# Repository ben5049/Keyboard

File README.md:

# Keyboard

## V3

Features:
- Wireless
    - 900mAh battery
    - Bluetooth (nRF52)
    - ZMK
- 4 Port USB hub
- BLDC Knob for haptic feedback
- Kailh Choc V1 switches

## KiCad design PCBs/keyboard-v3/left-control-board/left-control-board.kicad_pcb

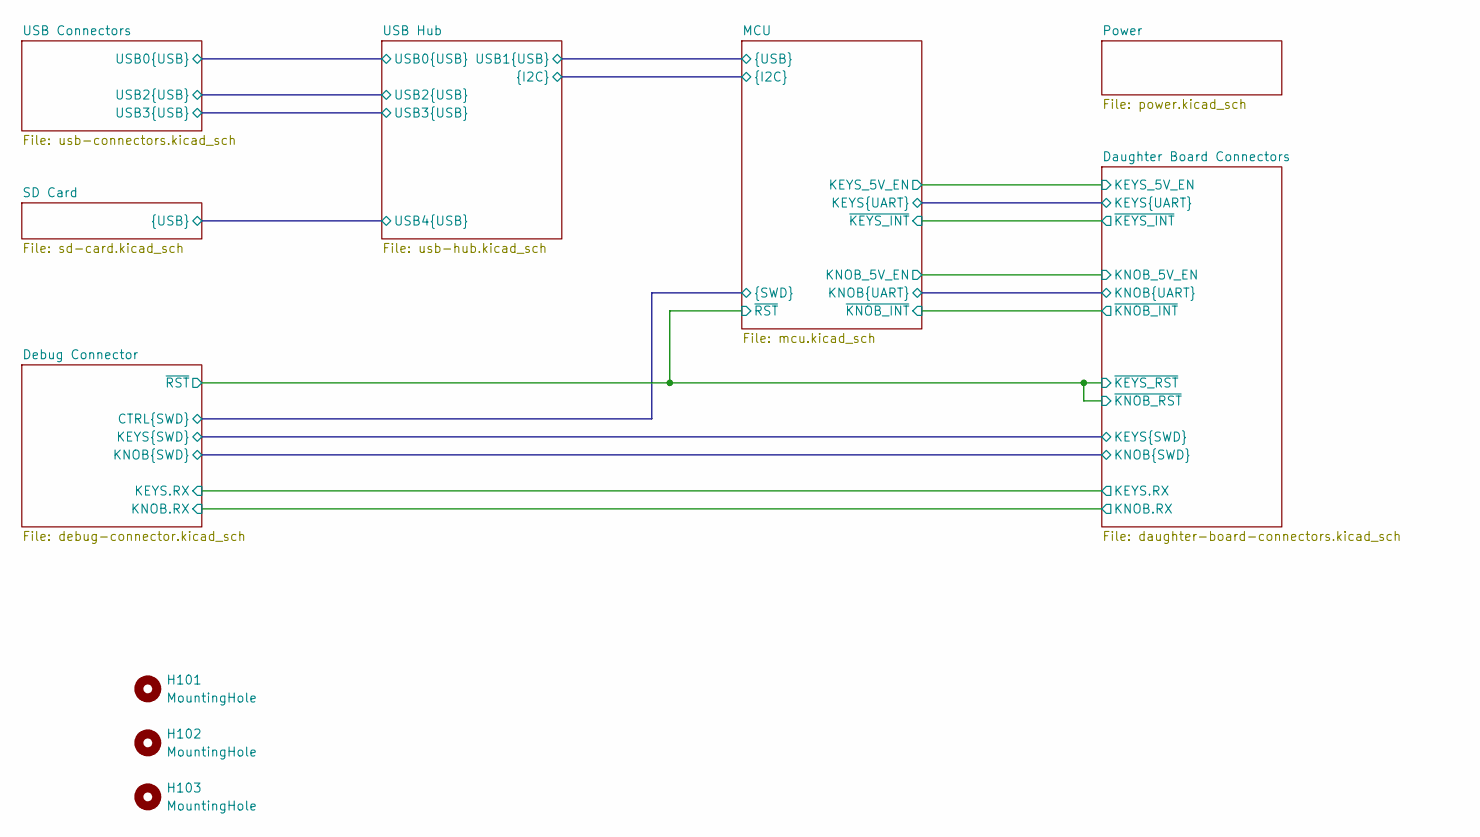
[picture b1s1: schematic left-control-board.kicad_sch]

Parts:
H101, H102, H103: MountingHole; MountingHole_2.2mm_M2

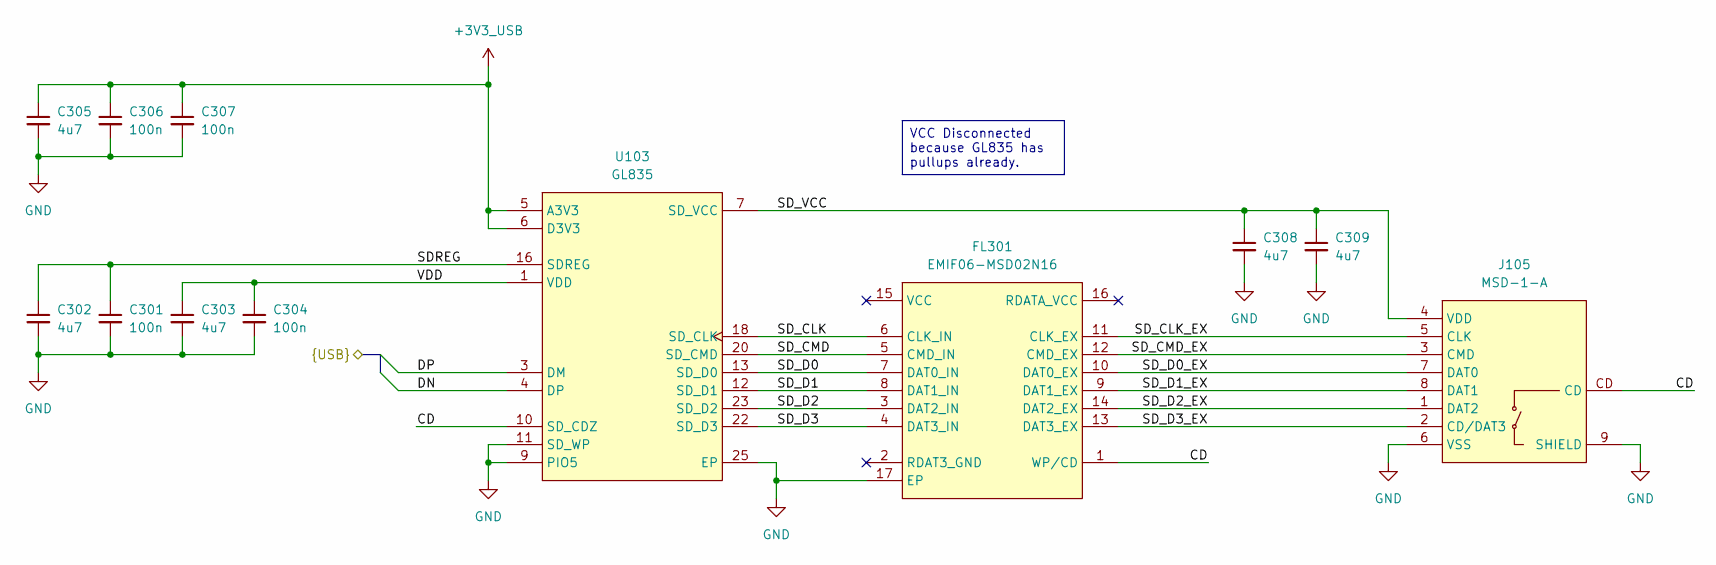
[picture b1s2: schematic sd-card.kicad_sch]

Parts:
C301, C304, C306, C307: 100n; C_0402
C302, C303, C305, C308, C309: 4u7; C_0402
FL301: EMIF06-MSD02N16; EMIF06MSD02N16
J105: MSD-1-A; MSD1A
U103: GL835; QFN50P400X400X100-25N-D

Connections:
+3V3_USB: C305.1, C306.1, C307.1, U103.5 (A3V3), U103.6 (D3V3); also elsewhere on the board
/SD Card/CD: FL301.1 (WP/CD), J105.CD, U103.10 (SD_CDZ)
/SD Card/DN: U103.4 (DP); also elsewhere on the board
/SD Card/DP: U103.3 (DM); also elsewhere on the board
/SD Card/SDREG: C301.1, C302.1, U103.16 (SDREG)
/SD Card/SD_CLK: FL301.6 (CLK_IN), U103.18 (SD_CLK)
/SD Card/SD_CLK_EX: FL301.11 (CLK_EX), J105.5 (CLK)
/SD Card/SD_CMD: FL301.5 (CMD_IN), U103.20 (SD_CMD)
/SD Card/SD_CMD_EX: FL301.12 (CMD_EX), J105.3 (CMD)
/SD Card/SD_D0: FL301.7 (DAT0_IN), U103.13 (SD_D0)
/SD Card/SD_D0_EX: FL301.10 (DAT0_EX), J105.7 (DAT0)
/SD Card/SD_D1: FL301.8 (DAT1_IN), U103.12 (SD_D1)
/SD Card/SD_D1_EX: FL301.9 (DAT1_EX), J105.8 (DAT1)
/SD Card/SD_D2: FL301.3 (DAT2_IN), U103.23 (SD_D2)
/SD Card/SD_D2_EX: FL301.14 (DAT2_EX), J105.1 (DAT2)
/SD Card/SD_D3: FL301.4 (DAT3_IN), U103.22 (SD_D3)
/SD Card/SD_D3_EX: FL301.13 (DAT3_EX), J105.2 (CD/DAT3)
/SD Card/SD_VCC: C308.1, C309.1, J105.4 (VDD), U103.7 (SD_VCC)
/SD Card/VDD: C303.1, C304.1, U103.1 (VDD)
GND: C301.2, C302.2, C303.2, C304.2, C305.2, C306.2, C307.2, C308.2, C309.2, FL301.17 (EP), J105.6 (VSS), J105.9 (SHIELD), J105.10 (SHIELD), J105.11 (SHIELD), J105.12 (SHIELD), U103.9 (PIO5), U103.11 (SD_WP), U103.25 (EP); also elsewhere on the board

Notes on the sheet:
VCC Disconnected because GL835 has pullups already.

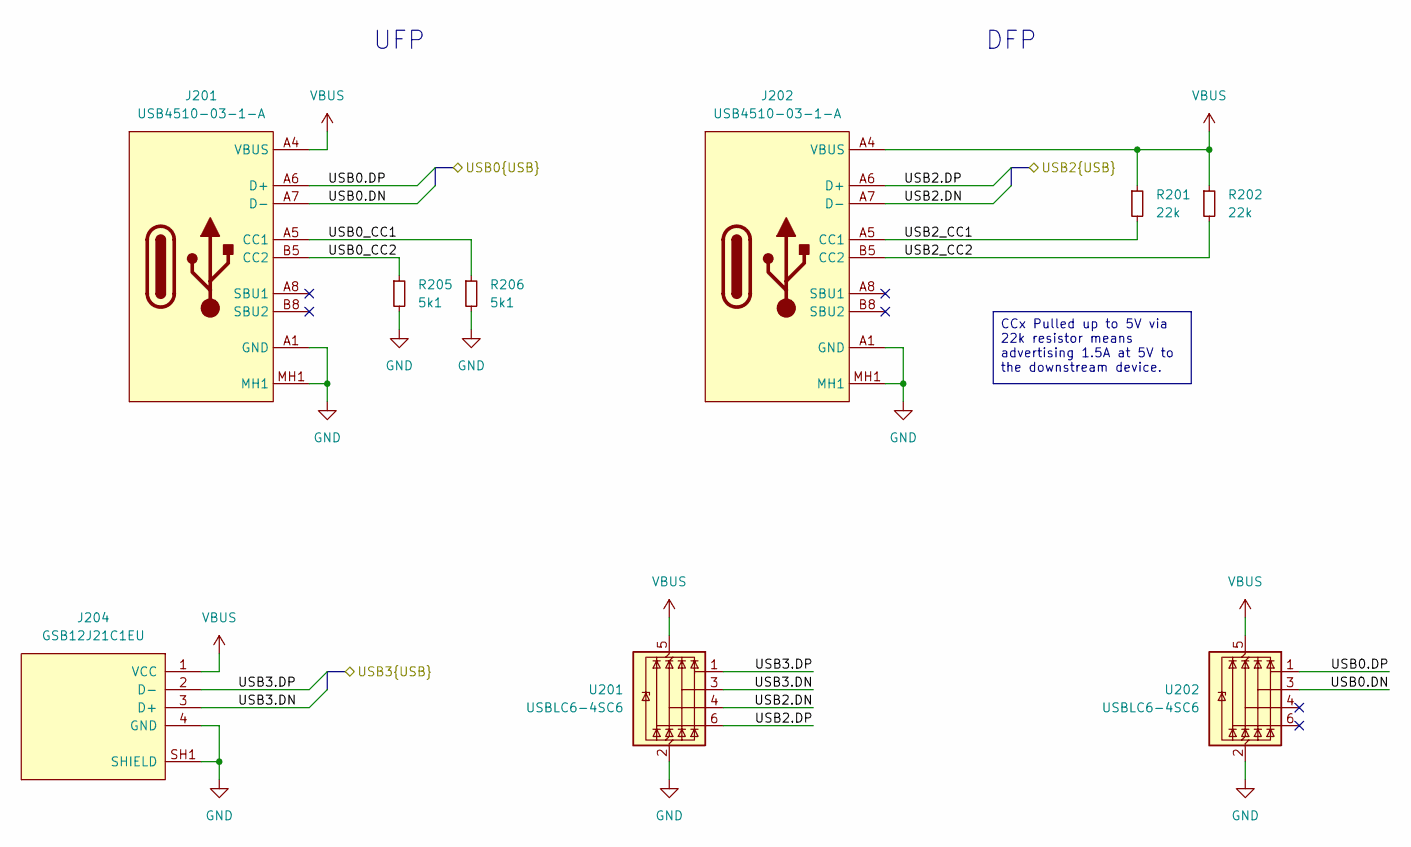
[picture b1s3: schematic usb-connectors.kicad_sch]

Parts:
J201, J202: USB4510-03-1-A; USB4510031A; Mouser Part Number 640-USB4510031A
J204: GSB12J21C1EU
R201, R202: 22k; R_0402
R205, R206: 5k1; R_0402
U201, U202: USBLC6-4SC6; SOT-23-6

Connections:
/USB Connectors/USB0.DN: J201.A7 (D-), J201.B7 (D-), U202.3 (I/O2); also elsewhere on the board
/USB Connectors/USB0.DP: J201.A6 (D+), J201.B6 (D+), U202.1 (I/O1); also elsewhere on the board
/USB Connectors/USB0_CC1: J201.A5 (CC1), R206.1
/USB Connectors/USB0_CC2: J201.B5 (CC2), R205.1
/USB Connectors/USB2.DN: J202.A7 (D-), J202.B7 (D-), U201.4 (I/O3); also elsewhere on the board
/USB Connectors/USB2.DP: J202.A6 (D+), J202.B6 (D+), U201.6 (I/O4); also elsewhere on the board
/USB Connectors/USB2_CC1: J202.A5 (CC1), R201.2
/USB Connectors/USB2_CC2: J202.B5 (CC2), R202.2
/USB Connectors/USB3.DN: J204.3 (D+), U201.3 (I/O2); also elsewhere on the board
/USB Connectors/USB3.DP: J204.2 (D-), U201.1 (I/O1); also elsewhere on the board
GND: J201.A1 (GND), J201.A12 (GND), J201.MH1, J201.MH2, J201.MH3, J201.MH4, J202.A1 (GND), J202.A12 (GND), J202.MH1, J202.MH2, J202.MH3, J202.MH4, J204.4 (GND), J204.SH1 (SHIELD), J204.SH2 (SHIELD), J204.SH3 (SHIELD), J204.SH4 (SHIELD), R205.2, R206.2, U201.2 (GND), U202.2 (GND); also elsewhere on the board
VBUS: J201.A4 (VBUS), J201.A9 (VBUS), J202.A4 (VBUS), J202.A9 (VBUS), J204.1 (VCC), R201.1, R202.1, U201.5 (VBUS), U202.5 (VBUS); also elsewhere on the board

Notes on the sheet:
UFP
DFP
CCx Pulled up to 5V via 22k resistor means advertising 1.5A at 5V to the downstream device.

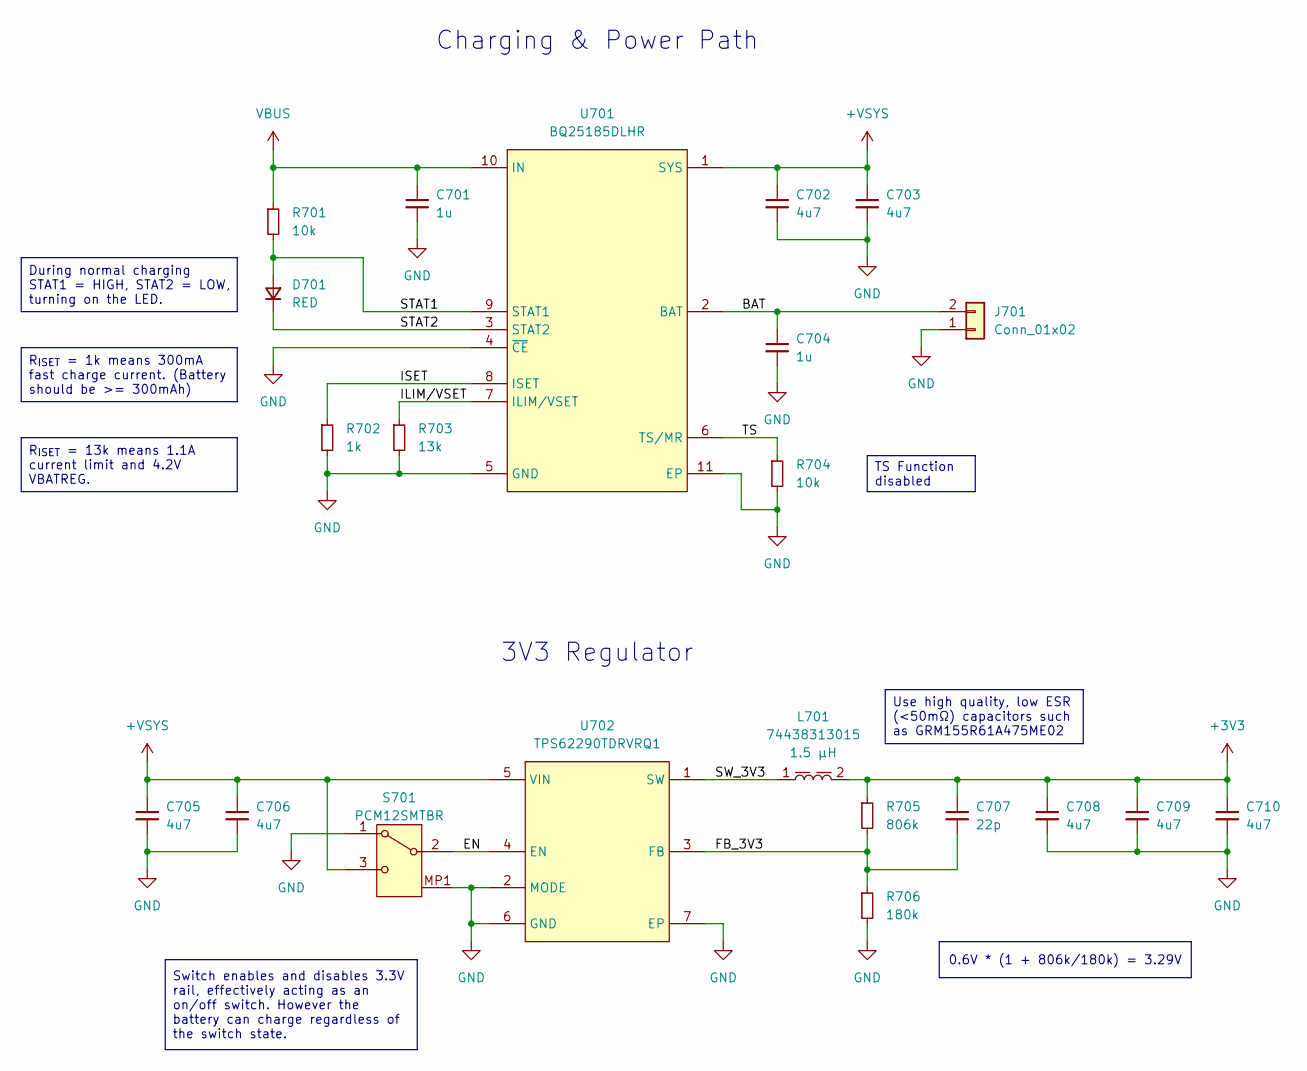
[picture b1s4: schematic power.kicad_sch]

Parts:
C701, C704: 1u; C_0402
C702, C703, C705, C706, C708, C709, C710: 4u7; C_0402
C707: 22p; C_0402
D701: RED; LED_0402
J701: Conn_01x02; JST_PH_S2B-PH-K_1x02_P2.00mm_Horizontal
L701: 74438313015; L_Wurth_WE-MAPI-1610; Part Number 74438313015
R701, R704: 10k; R_0402
R702: 1k; R_0402
R703: 13k; R_0402
R705: 806k; R_0402
R706: 180k; R_0402
S701: PCM12SMTBR
U701: BQ25185DLHR; SON40P220X200X80-11N
U702: TPS62290TDRVRQ1; SON65P200X200X80-7N; Mouser Part Number 595-TPS62290TDRVRQ1

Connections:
+3V3: C707.1, C708.1, C709.1, C710.1, L701.2, R705.1; also elsewhere on the board
+VSYS: C702.1, C703.1, C705.1, C706.1, S701.3 (NO), U701.1 (SYS), U702.5 (VIN); also elsewhere on the board
/Power/BAT: C704.1, J701.2, U701.2 (BAT)
/Power/EN: S701.2 (COM), U702.4 (EN)
/Power/FB_3V3: C707.2, R705.2, R706.1, U702.3 (FB)
/Power/ILIM/VSET: R703.1, U701.7 (ILIM/VSET)
/Power/ISET: R702.1, U701.8 (ISET)
/Power/STAT1: D701.2 (A), R701.2, U701.9 (STAT1)
/Power/STAT2: D701.1 (K), U701.3 (STAT2)
/Power/SW_3V3: L701.1, U702.1 (SW)
/Power/TS: R704.1, U701.6 (TS/MR)
GND: C701.2, C702.2, C703.2, C704.2, C705.2, C706.2, C708.2, C709.2, C710.2, J701.1, R702.2, R703.2, R704.2, R706.2, S701.1 (NC), S701.MP1, S701.MP2, S701.MP3, S701.MP4, U701.4 (~CE), U701.5 (GND), U701.11 (EP), U702.2 (MODE), U702.6 (GND), U702.7 (EP); also elsewhere on the board
VBUS: C701.1, R701.1, U701.10 (IN); also elsewhere on the board

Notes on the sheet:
3V3 Regulator
Charging & Power Path
Switch enables and disables 3.3V rail, effectively acting as an on/off switch. However the battery can charge regardless of the switch state.
0.6V * (1 + 806k/180k) = 3.29V
During normal charging STAT1 = HIGH, STAT2 = LOW, turning on the LED.
Use high quality, low ESR (<50mΩ) capacitors such as GRM155R61A475ME02
R_{ISET} = 1k means 300mA fast charge current. (Battery should be >= 300mAh)
R_{ISET} = 13k means 1.1A current limit and 4.2V VBATREG.
TS Function disabled

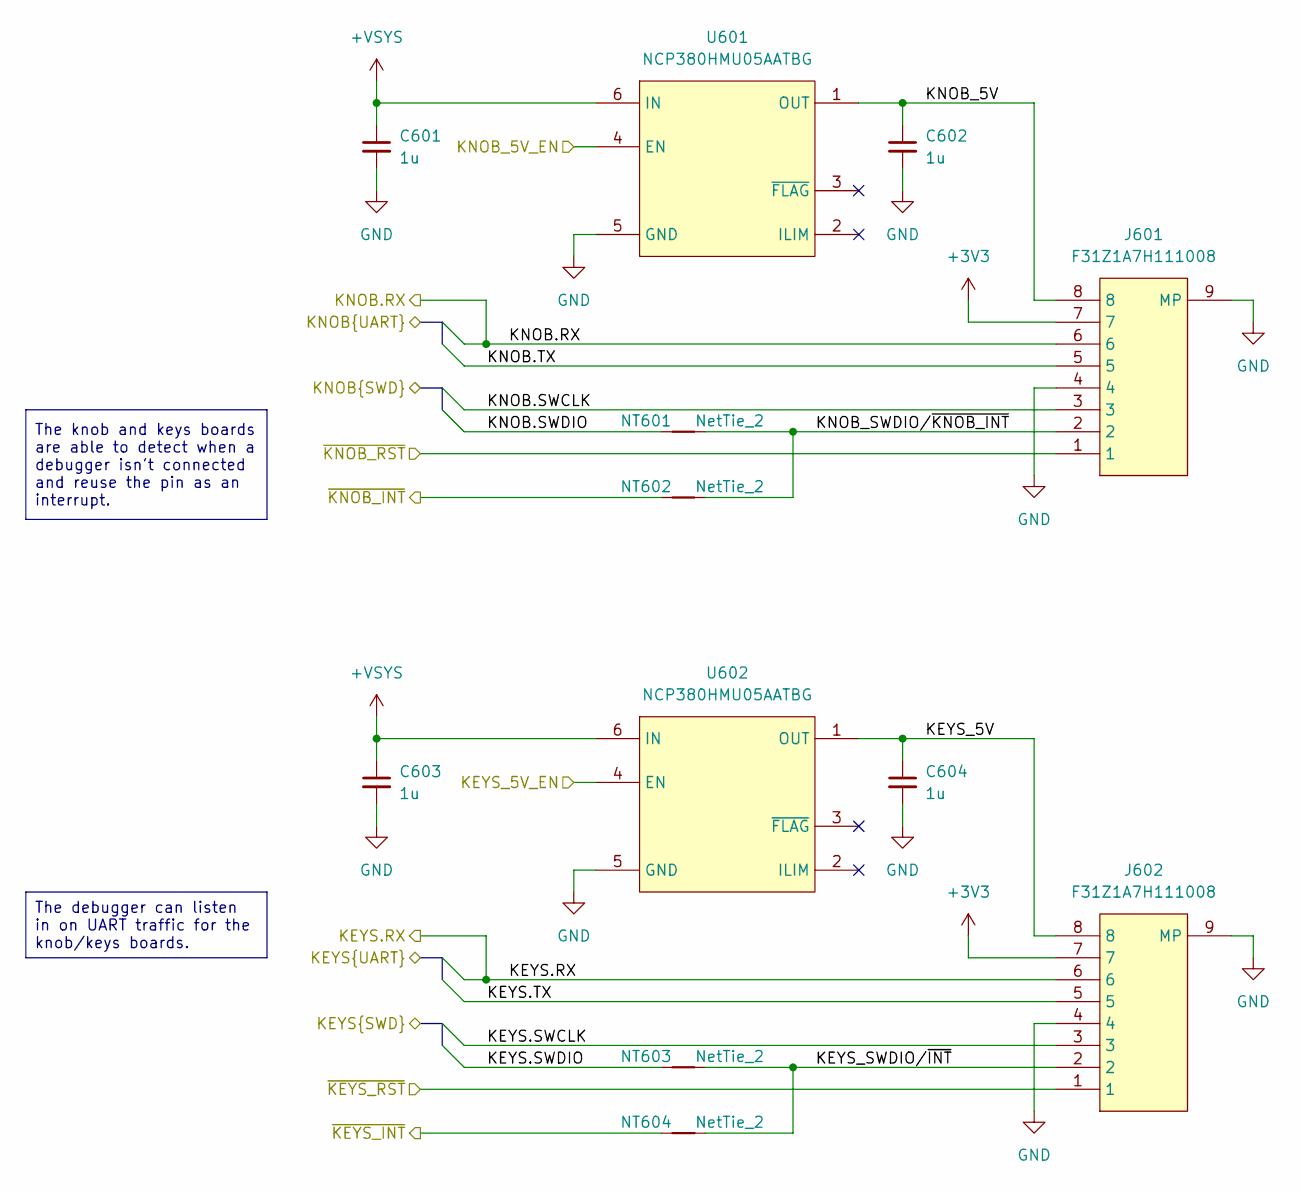
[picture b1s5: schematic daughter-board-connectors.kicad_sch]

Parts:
C601, C602, C603, C604: 1u; C_0402
J601, J602: F31Z1A7H111008
NT601, NT602, NT603, NT604: NetTie_2; NetTie-2_SMD_Pad0.15mm
U601, U602: NCP380HMU05AATBG; SON65P200X200X55-7N

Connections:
+3V3: J601.7, J602.7; also elsewhere on the board
+VSYS: C601.1, C603.1, U601.6 (IN), U602.6 (IN); also elsewhere on the board
/Daughter Board Connectors/KEYS.RX: J602.6; also elsewhere on the board
/Daughter Board Connectors/KEYS.SWCLK: J602.3; also elsewhere on the board
/Daughter Board Connectors/KEYS.SWDIO: NT603.1; also elsewhere on the board
/Daughter Board Connectors/KEYS.TX: J602.5; also elsewhere on the board
/Daughter Board Connectors/KEYS_5V: C604.1, J602.8, U602.1 (OUT)
/Daughter Board Connectors/KEYS_5V_EN: U602.4 (EN); also elsewhere on the board
/Daughter Board Connectors/KEYS_SWDIO/~INT: J602.2, NT603.2, NT604.2
/Daughter Board Connectors/KNOB.RX: J601.6; also elsewhere on the board
/Daughter Board Connectors/KNOB.SWCLK: J601.3; also elsewhere on the board
/Daughter Board Connectors/KNOB.SWDIO: NT601.1; also elsewhere on the board
/Daughter Board Connectors/KNOB.TX: J601.5; also elsewhere on the board
/Daughter Board Connectors/KNOB_5V: C602.1, J601.8, U601.1 (OUT)
/Daughter Board Connectors/KNOB_5V_EN: U601.4 (EN); also elsewhere on the board
/Daughter Board Connectors/KNOB_SWDIO/~KNOB_INT: J601.2, NT601.2, NT602.2
/Daughter Board Connectors/~KEYS_INT: NT604.1; also elsewhere on the board
/Daughter Board Connectors/~KEYS_RST: J601.1, J602.1; also elsewhere on the board
/Daughter Board Connectors/~KNOB_INT: NT602.1; also elsewhere on the board
GND: C601.2, C602.2, C603.2, C604.2, J601.4, J601.9 (MP), J601.10 (MP), J601.11 (MP), J601.12 (MP), J602.4, J602.9 (MP), J602.10 (MP), J602.11 (MP), J602.12 (MP), U601.5 (GND), U601.7 (GND), U602.5 (GND), U602.7 (GND); also elsewhere on the board

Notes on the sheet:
The debugger can listen in on UART traffic for the knob/keys boards.
The knob and keys boards are able to detect when a debugger isn't connected and reuse the pin as an interrupt.

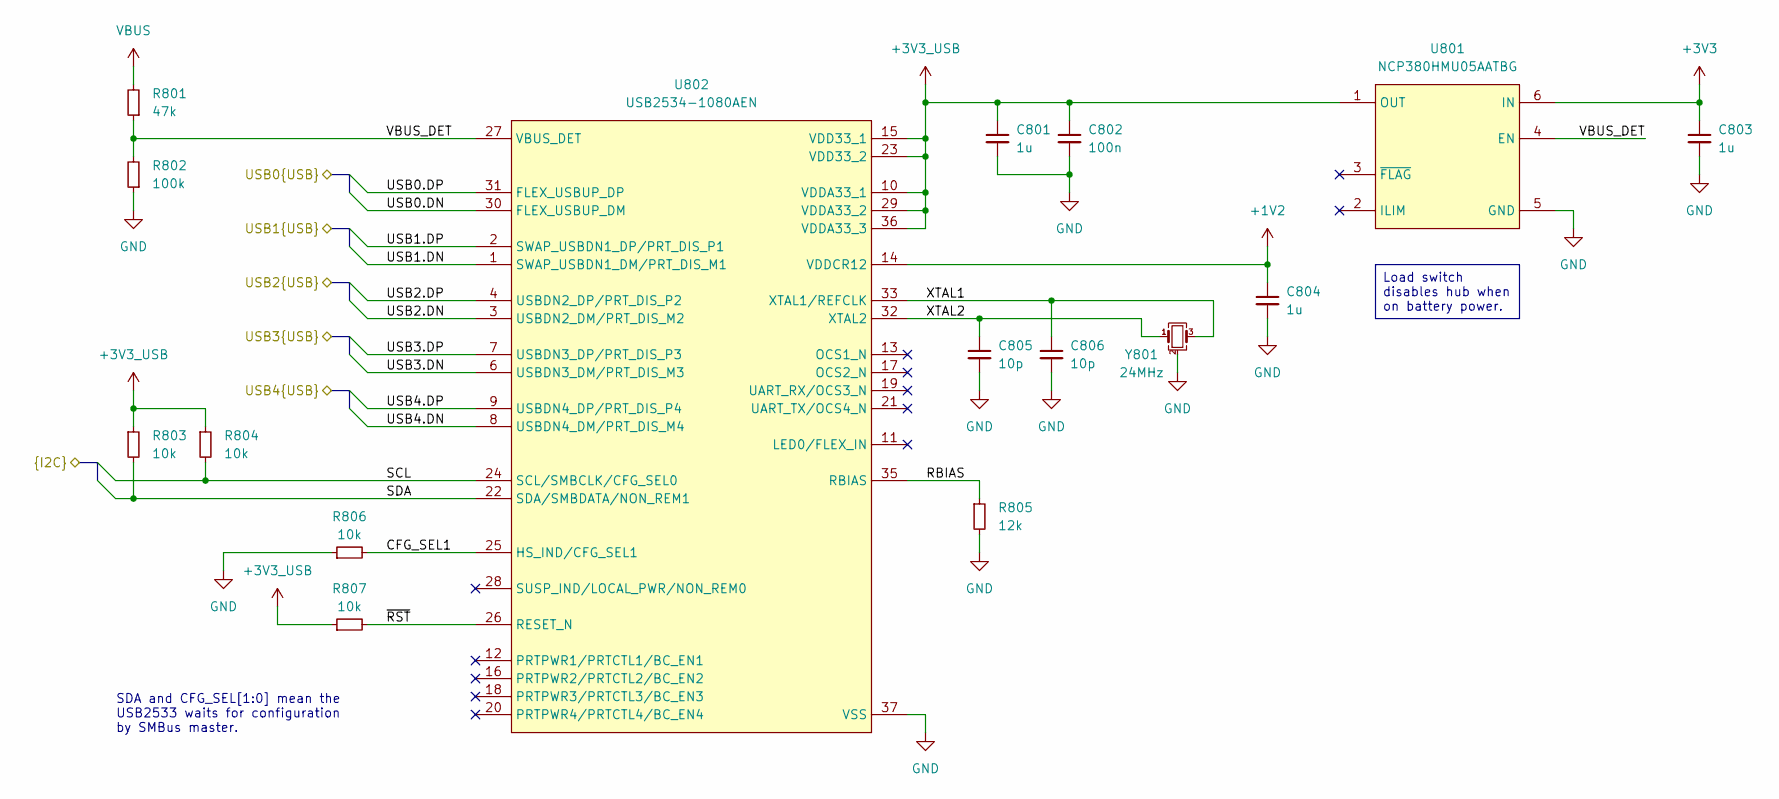
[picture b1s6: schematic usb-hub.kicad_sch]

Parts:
C801, C803, C804: 1u; C_0402
C802: 100n; C_0402
C805, C806: 10p; C_0402
R801: 47k; R_0402
R802: 100k; R_0402
R803, R804, R806, R807: 10k; R_0402
R805: 12k; R_0402
U801: NCP380HMU05AATBG; SON65P200X200X55-7N
U802: USB2534-1080AEN; QFN50P600X600X100-37N-D
Y801: CX2016SA24000D0HLLG3; Crystal_SMD_2016-4Pin_2.0x1.6mm

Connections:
+1V2: C804.1, U802.14 (VDDCR12)
+3V3: C803.1, U801.6 (IN); also elsewhere on the board
+3V3_USB: C801.1, C802.1, R803.1, R804.1, R807.1, U801.1 (OUT), U802.10 (VDDA33_1), U802.15 (VDD33_1), U802.23 (VDD33_2), U802.29 (VDDA33_2), U802.36 (VDDA33_3); also elsewhere on the board
/MCU/DN: U802.1 (SWAP_USBDN1_DM/PRT_DIS_M1); also elsewhere on the board
/MCU/DP: U802.2 (SWAP_USBDN1_DP/PRT_DIS_P1); also elsewhere on the board
/MCU/SCL: R804.2, U802.24 (SCL/SMBCLK/CFG_SEL0); also elsewhere on the board
/MCU/SDA: R803.2, U802.22 (SDA/SMBDATA/NON_REM1); also elsewhere on the board
/SD Card/DN: U802.8 (USBDN4_DM/PRT_DIS_M4); also elsewhere on the board
/SD Card/DP: U802.9 (USBDN4_DP/PRT_DIS_P4); also elsewhere on the board
/USB Connectors/USB0.DN: U802.30 (FLEX_USBUP_DM); also elsewhere on the board
/USB Connectors/USB0.DP: U802.31 (FLEX_USBUP_DP); also elsewhere on the board
/USB Connectors/USB2.DN: U802.3 (USBDN2_DM/PRT_DIS_M2); also elsewhere on the board
/USB Connectors/USB2.DP: U802.4 (USBDN2_DP/PRT_DIS_P2); also elsewhere on the board
/USB Connectors/USB3.DN: U802.6 (USBDN3_DM/PRT_DIS_M3); also elsewhere on the board
/USB Connectors/USB3.DP: U802.7 (USBDN3_DP/PRT_DIS_P3); also elsewhere on the board
/USB Hub/CFG_SEL1: R806.2, U802.25 (HS_IND/CFG_SEL1)
/USB Hub/RBIAS: R805.1, U802.35 (RBIAS)
/USB Hub/VBUS_DET: R801.1, R802.2, U801.4 (EN), U802.27 (VBUS_DET)
/USB Hub/XTAL1: C806.1, U802.33 (XTAL1/REFCLK), Y801.3
/USB Hub/XTAL2: C805.1, U802.32 (XTAL2), Y801.1
/USB Hub/~RST: R807.2, U802.26 (RESET_N)
GND: C801.2, C802.2, C803.2, C804.2, C805.2, C806.2, R802.1, R805.2, R806.1, U801.5 (GND), U801.7 (GND), U802.37 (VSS), Y801.2 (G), Y801.4 (G); also elsewhere on the board
VBUS: R801.2; also elsewhere on the board

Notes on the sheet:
SDA and CFG_SEL[1:0] mean the USB2533 waits for configuration by SMBus master.
Load switch disables hub when on battery power.

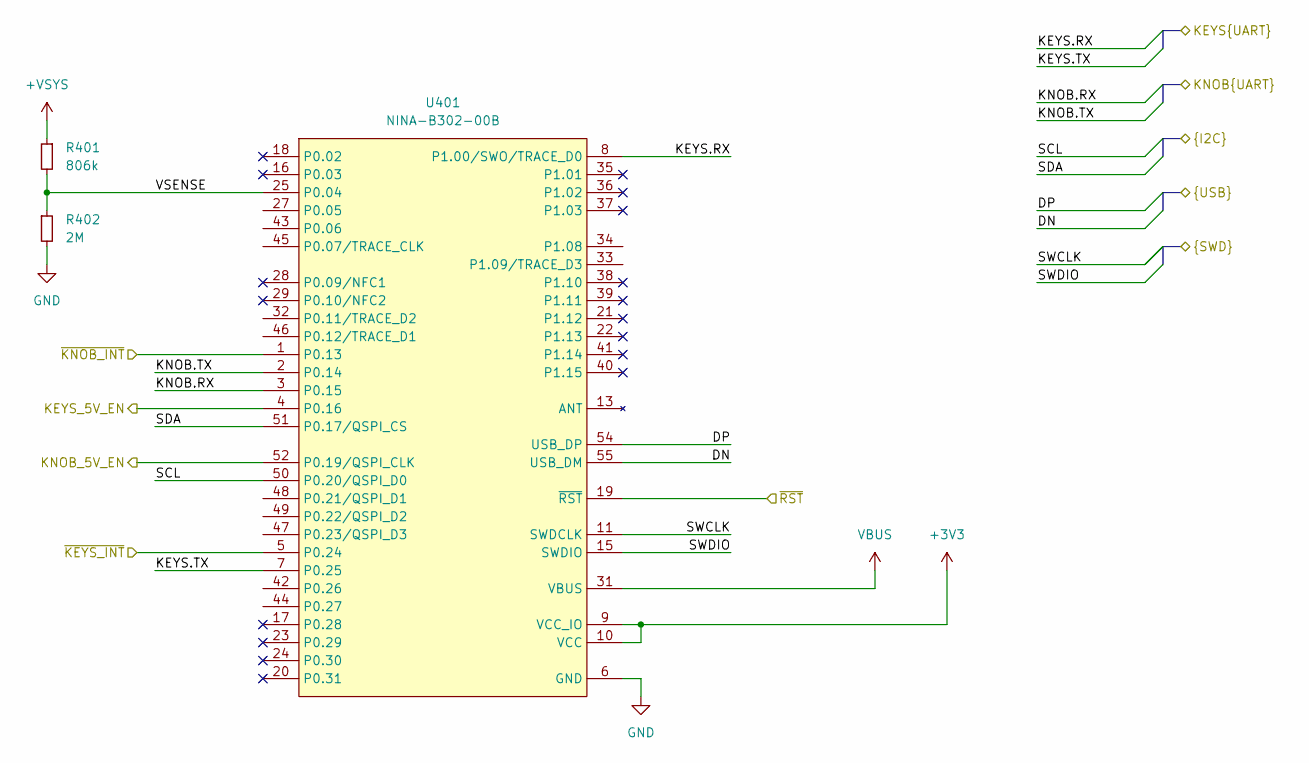
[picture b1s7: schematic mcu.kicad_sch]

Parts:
R401: 806k; R_0402
R402: 2M; R_0402
U401: NINA-B302-00B; NINAB30200B

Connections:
+3V3: U401.9 (VCC_IO), U401.10 (VCC); also elsewhere on the board
+VSYS: R401.1; also elsewhere on the board
/Daughter Board Connectors/KEYS.RX: U401.8 (P1.00/SWO/TRACE_D0); also elsewhere on the board
/Daughter Board Connectors/KEYS.TX: U401.7 (P0.25); also elsewhere on the board
/Daughter Board Connectors/KEYS_5V_EN: U401.4 (P0.16); also elsewhere on the board
/Daughter Board Connectors/KNOB.RX: U401.3 (P0.15); also elsewhere on the board
/Daughter Board Connectors/KNOB.TX: U401.2 (P0.14); also elsewhere on the board
/Daughter Board Connectors/KNOB_5V_EN: U401.52 (P0.19/QSPI_CLK); also elsewhere on the board
/Daughter Board Connectors/~KEYS_INT: U401.5 (P0.24); also elsewhere on the board
/Daughter Board Connectors/~KEYS_RST: U401.19 (~RST); also elsewhere on the board
/Daughter Board Connectors/~KNOB_INT: U401.1 (P0.13); also elsewhere on the board
/Debug Connector/CTRL.SWCLK: U401.11 (SWDCLK); also elsewhere on the board
/Debug Connector/CTRL.SWDIO: U401.15 (SWDIO); also elsewhere on the board
/MCU/DN: U401.55 (USB_DM); also elsewhere on the board
/MCU/DP: U401.54 (USB_DP); also elsewhere on the board
/MCU/SCL: U401.50 (P0.20/QSPI_D0); also elsewhere on the board
/MCU/SDA: U401.51 (P0.17/QSPI_CS); also elsewhere on the board
/MCU/VSENSE: R401.2, R402.1, U401.25 (P0.04)
GND: R402.2, U401.6 (GND), U401.12 (GND), U401.14 (GND), U401.26 (GND), U401.30 (GND), U401.53 (GND), U401.56 (GND), U401.57 (GND), U401.58 (GND), U401.59 (GND), U401.60 (GND), U401.61 (GND), U401.62 (GND), U401.63 (GND), U401.64 (GND), U401.65 (GND), U401.66 (GND), U401.67 (GND); also elsewhere on the board
VBUS: U401.31 (VBUS); also elsewhere on the board

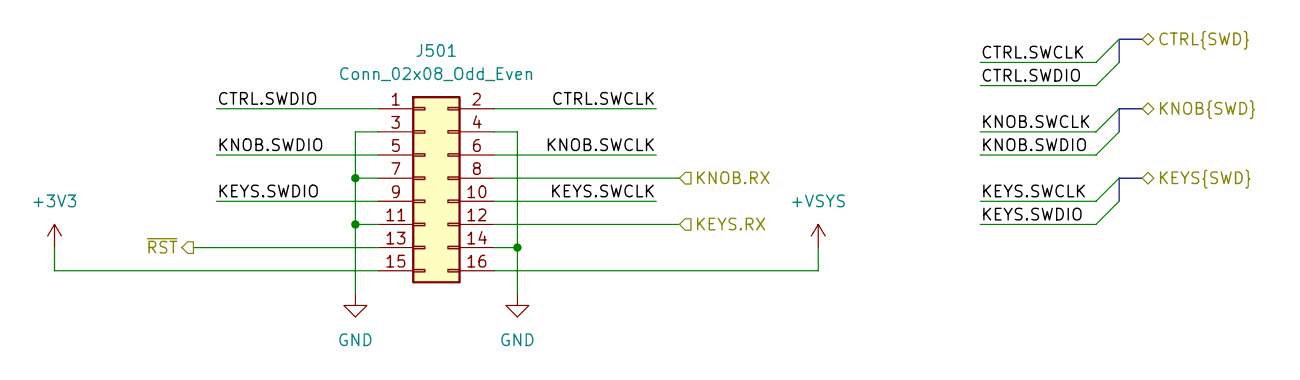
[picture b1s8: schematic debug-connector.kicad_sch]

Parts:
J501: Conn_02x08_Odd_Even; PinSocket_2x08_P1.27mm_Horizontal

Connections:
+3V3: J501.15; also elsewhere on the board
+VSYS: J501.16; also elsewhere on the board
/Daughter Board Connectors/KEYS.RX: J501.12; also elsewhere on the board
/Daughter Board Connectors/KEYS.SWCLK: J501.10; also elsewhere on the board
/Daughter Board Connectors/KEYS.SWDIO: J501.9; also elsewhere on the board
/Daughter Board Connectors/KNOB.RX: J501.8; also elsewhere on the board
/Daughter Board Connectors/KNOB.SWCLK: J501.6; also elsewhere on the board
/Daughter Board Connectors/KNOB.SWDIO: J501.5; also elsewhere on the board
/Daughter Board Connectors/~KEYS_RST: J501.13; also elsewhere on the board
/Debug Connector/CTRL.SWCLK: J501.2; also elsewhere on the board
/Debug Connector/CTRL.SWDIO: J501.1; also elsewhere on the board
GND: J501.3, J501.4, J501.7, J501.11, J501.14; also elsewhere on the board

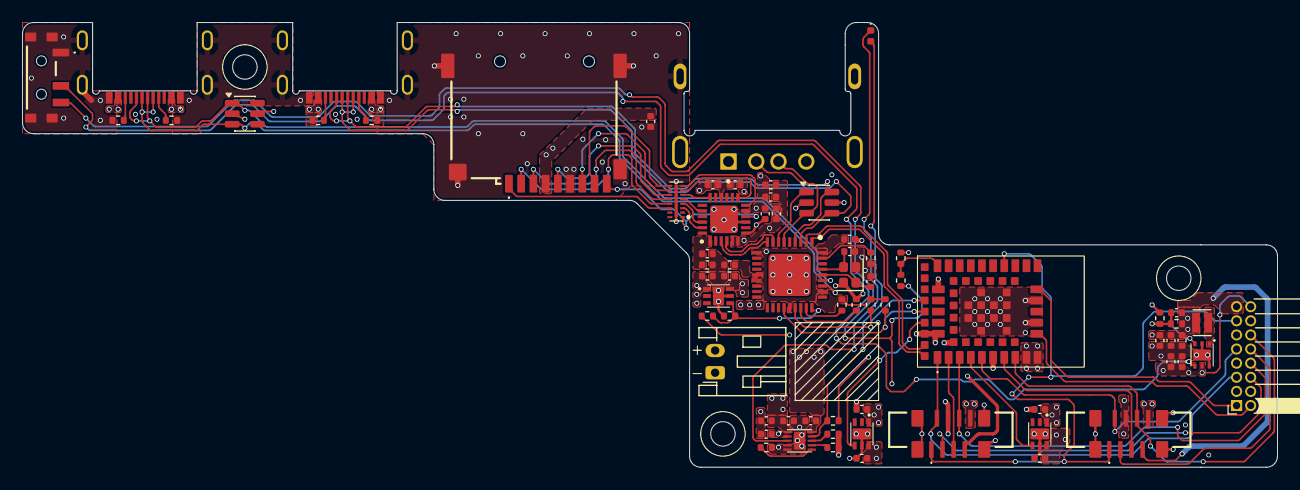
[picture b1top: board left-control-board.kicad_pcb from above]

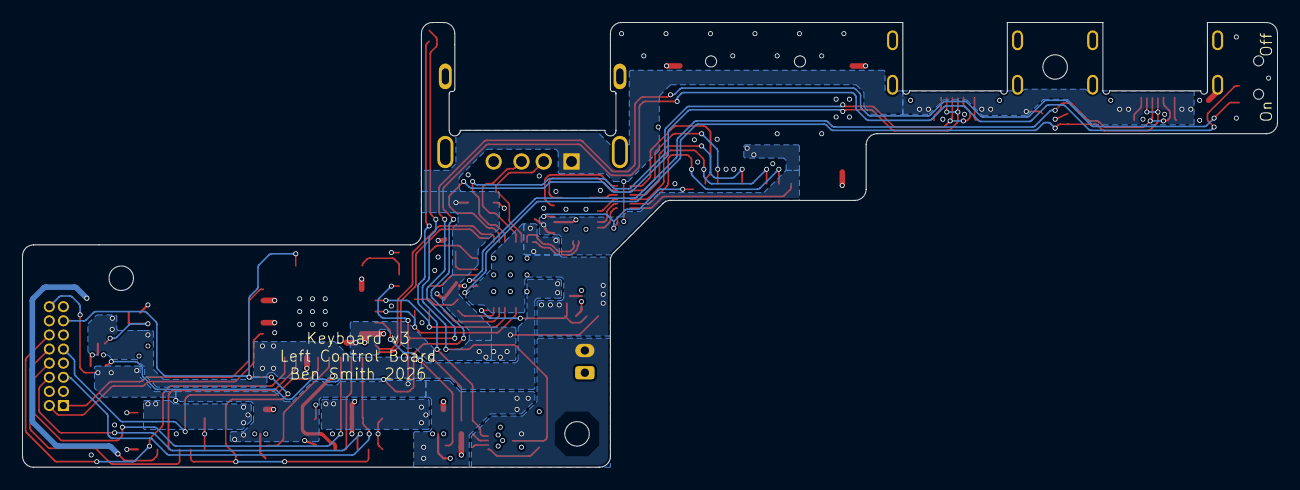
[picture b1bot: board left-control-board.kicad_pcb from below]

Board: 4 copper layers, 112.9 x 40.0 mm, 78 parts (2 on the bottom side), 73 nets.

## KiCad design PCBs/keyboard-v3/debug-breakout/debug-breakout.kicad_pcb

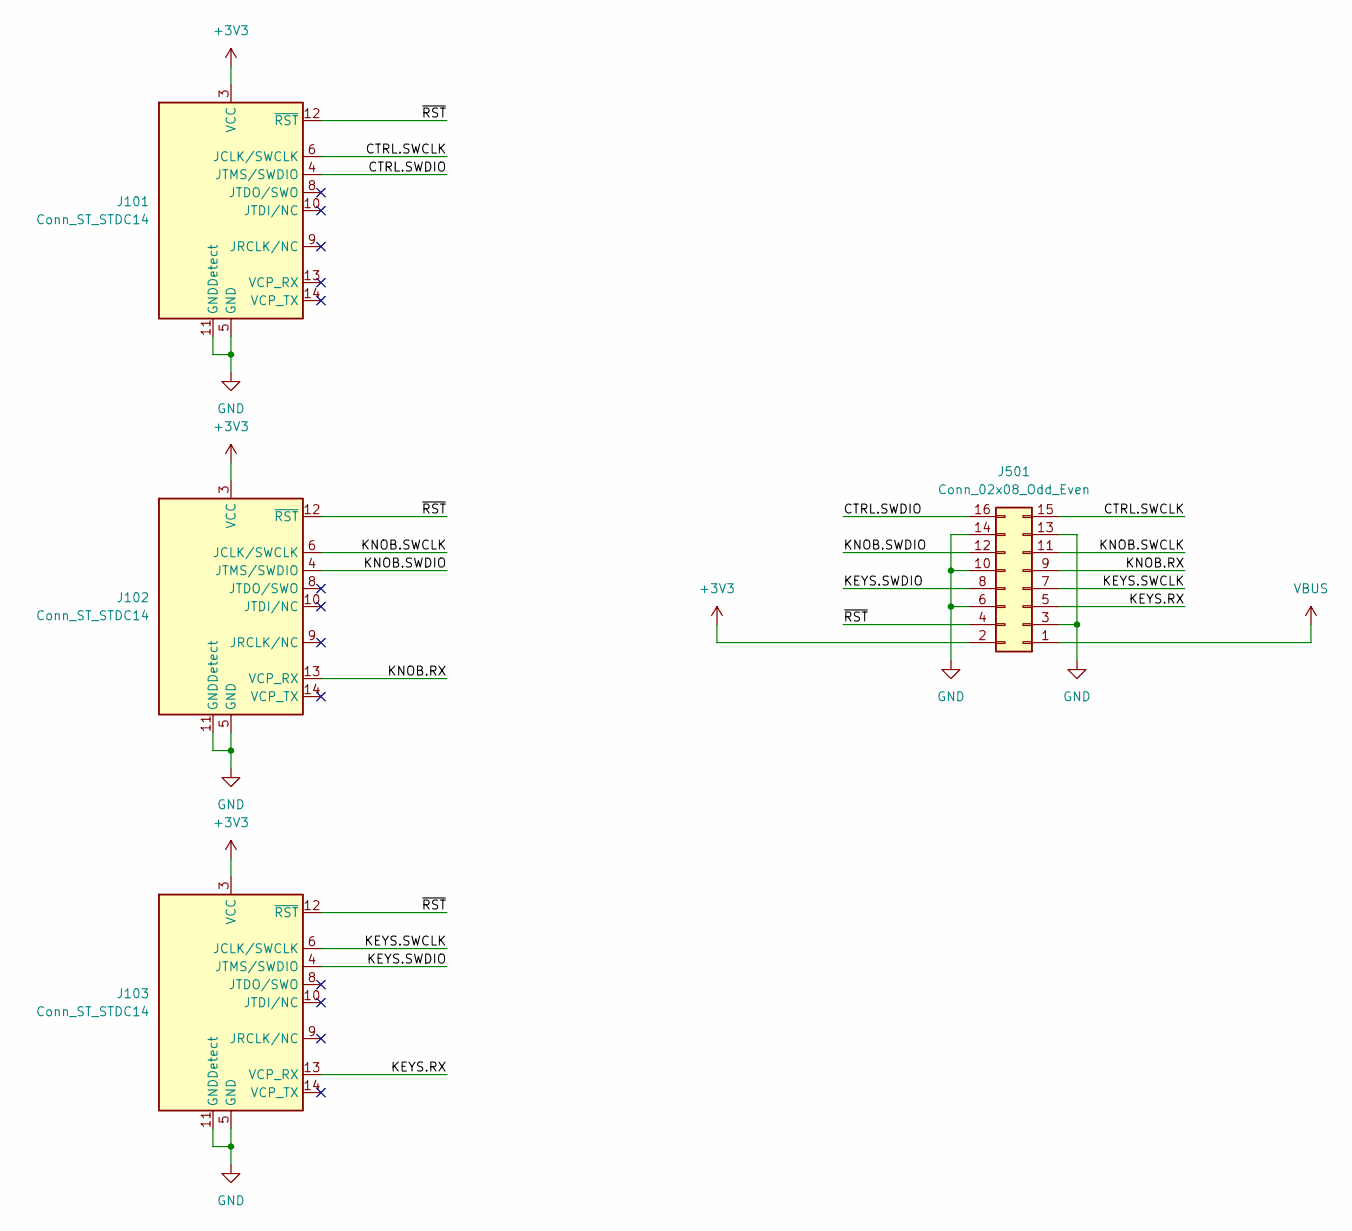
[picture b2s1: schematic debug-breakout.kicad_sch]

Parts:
J101, J102, J103: Conn_ST_STDC14; STDC14
J501: Conn_02x08_Odd_Even; PinHeader_2x08_P1.27mm_Horizontal

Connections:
+3V3: J101.3 (VCC), J102.3 (VCC), J103.3 (VCC), J501.2
/CTRL.SWCLK: J101.6 (JCLK/SWCLK), J501.15
/CTRL.SWDIO: J101.4 (JTMS/SWDIO), J501.16
/KEYS.RX: J103.13 (VCP_RX), J501.5
/KEYS.SWCLK: J103.6 (JCLK/SWCLK), J501.7
/KEYS.SWDIO: J103.4 (JTMS/SWDIO), J501.8
/KNOB.RX: J102.13 (VCP_RX), J501.9
/KNOB.SWCLK: J102.6 (JCLK/SWCLK), J501.11
/KNOB.SWDIO: J102.4 (JTMS/SWDIO), J501.12
/~RST: J101.12 (~RST), J102.12 (~RST), J103.12 (~RST), J501.4
GND: J101.5 (GND), J101.7 (GND), J101.11 (GNDDetect), J102.5 (GND), J102.7 (GND), J102.11 (GNDDetect), J103.5 (GND), J103.7 (GND), J103.11 (GNDDetect), J501.3, J501.6, J501.10, J501.13, J501.14
VBUS: J501.1

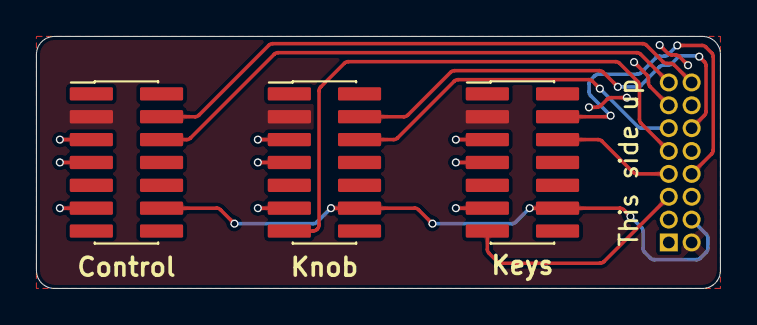
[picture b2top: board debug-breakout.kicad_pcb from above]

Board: 2 copper layers, 38.0 x 14.0 mm, 4 parts (1 on the bottom side), 11 nets.

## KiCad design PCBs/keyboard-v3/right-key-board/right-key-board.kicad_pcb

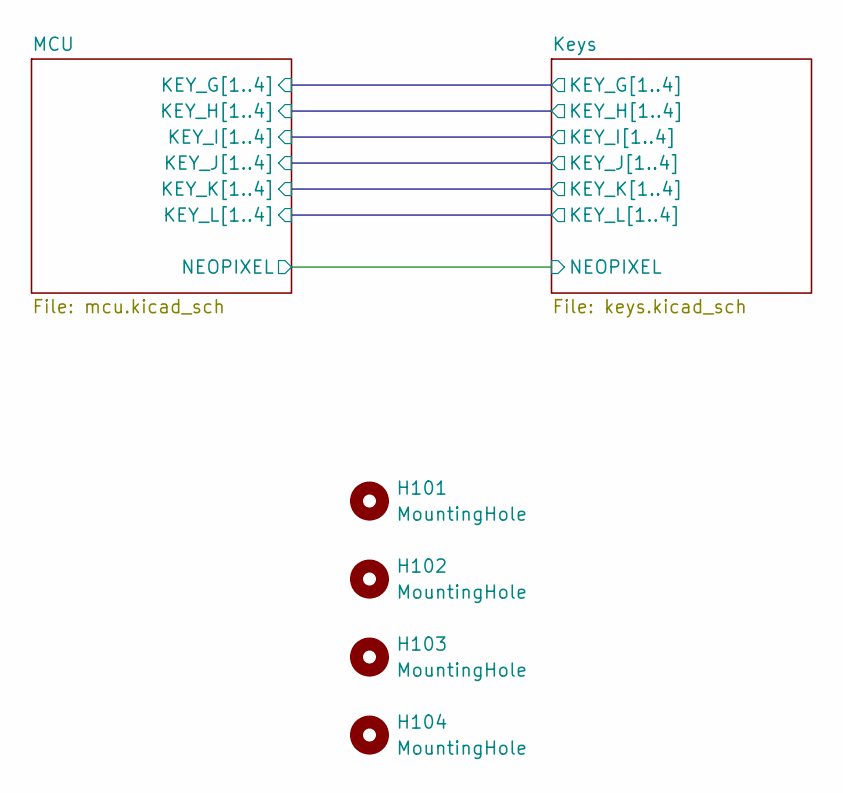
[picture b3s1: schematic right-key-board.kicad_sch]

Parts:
H101, H102, H103, H104: MountingHole; MountingHole_2.2mm_M2
